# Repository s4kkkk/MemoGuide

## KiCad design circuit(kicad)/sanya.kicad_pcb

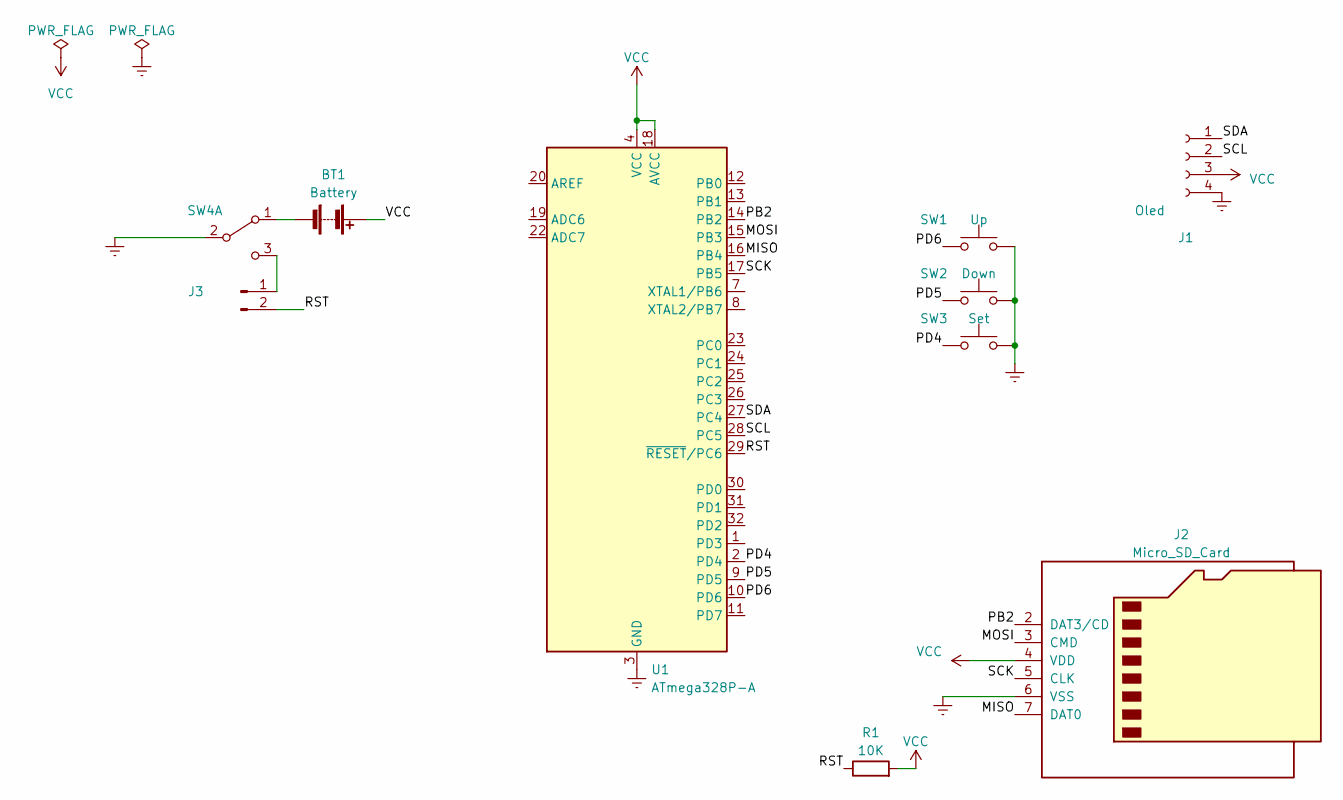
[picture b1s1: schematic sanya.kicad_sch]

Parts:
BT1: Battery; CR2032_BatteryHolder
J1: Oled; PinHeader_1x04_P2.54mm_Vertical
J2: Micro_SD_Card; microSD_HC_Wuerth_693072010801
J3: sw1; PinHeader_1x02_P2.54mm_Vertical
R1: 10K; R_1812_4532Metric_Pad1.30x3.40mm_HandSolder
SW1: Up; Button
SW2: Down; Button
SW3: Set; Button
SW4: SW_DPDT_x2; SW_SPDT_PCM12
U1: ATmega328P-A; TQFP-32_7x7mm_P0.8mm

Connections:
/MISO: J2.7 (DAT0), U1.16 (PB4)
/MOSI: J2.3 (CMD), U1.15 (PB3)
/PB2: J2.2 (DAT3/CD), U1.14 (PB2)
/PD4: SW3.1, U1.2 (PD4)
/PD5: SW2.1, U1.9 (PD5)
/PD6: SW1.1, U1.10 (PD6)
/RST: J3.2, R1.1, U1.29 (~RESET/PC6)
/SCK: J2.5 (CLK), U1.17 (PB5)
/SCL: J1.2, U1.28 (PC5)
/SDA: J1.1, U1.27 (PC4)
Earth: J1.4, J2.6 (VSS), SW1.2, SW2.2, SW3.2, SW4.2 (B), U1.3 (GND), U1.5 (GND), U1.21 (GND)
unnamed: BT1.2 (-), SW4.1 (A)
unnamed: J3.1, SW4.3 (C)
VCC: BT1.1 (+), J1.3, J2.4 (VDD), R1.2, U1.4 (VCC), U1.6 (VCC), U1.18 (AVCC)

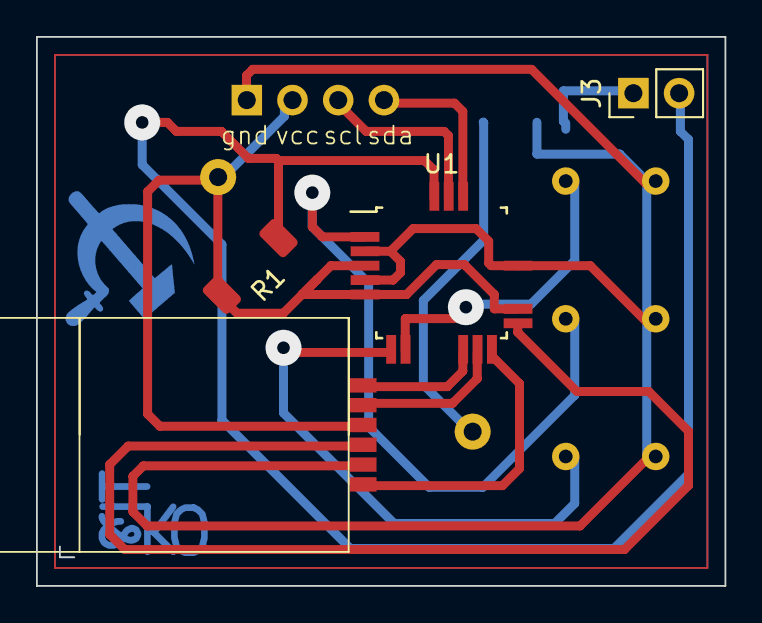
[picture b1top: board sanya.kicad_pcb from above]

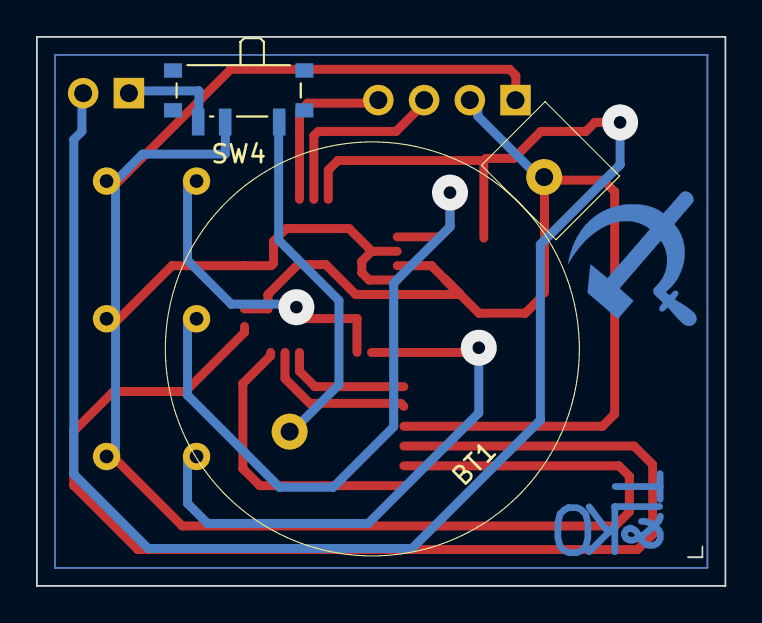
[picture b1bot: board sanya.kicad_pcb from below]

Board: 2 copper layers, 38.2 x 30.5 mm, 10 parts (2 on the bottom side), 14 nets.

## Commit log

2023-05-15 BEGIN
2023-05-15 sshnk1
2023-05-16 Изменил размер дорожек и переходных отверстий
2023-05-16 Подкорректировал посадочные места, провел дорожки автотрассировщиком (еще не финальный вариант)
2023-05-20 Дорожки вроде как протрассированы финально. Осталось увеличить между ними расстояние и некоторые переходные отверстия отодвинуть (смотри по 3D-чертежу, там видно, что некоторые компоненты закрывают п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
2023-05-21 Трассировка завершена. Остались финальные штрихи: подровнять всё, добавить медную окантовку
2023-05-23 изменил посадочное под выключатель
2023-05-25 Изменил посадочное место для батарейки; Заново протрассировал дорожки
2023-05-25 подвигал дорожки, добавил лого :)
2023-05-26 v 1.0: Release
2023-05-29 Убрал ненужные контактные площадки, увеличил размеры площадок под кнопки, убрал переходное под МК
2023-05-31 Сделал перемычку м/у RST и GND
